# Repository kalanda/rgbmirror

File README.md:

# RGB Mirror

Controller based on Atmega8 used for modification of a Muppet's mirror to use RGB Leds.

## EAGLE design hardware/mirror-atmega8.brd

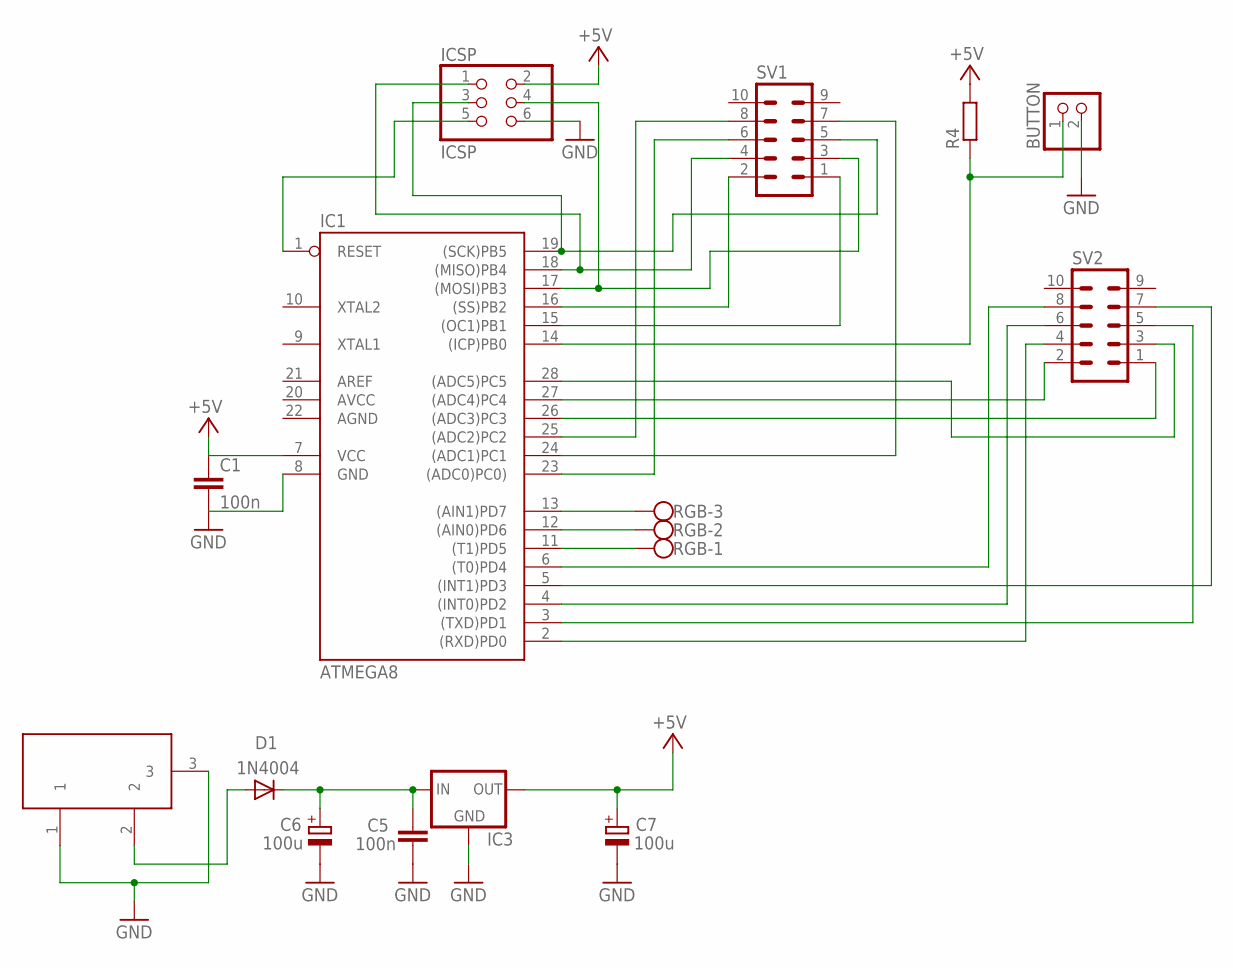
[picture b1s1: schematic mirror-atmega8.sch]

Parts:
BUTTON: PINHD-1X2; 1X02
C1, C5: 100n; C050-025X075
C6, C7: 100u; E3,5-8
D1: 1N4004; DO41-10
DC1: DC21MMX; DC-21MM
IC1: ATMEGA8; DIL28-3
IC3: 78XXL
ICSP: ICSP; 2X03
R4: R-EU_0204/7; 0204/7
RGB: W237-103
SV1, SV2: ML10

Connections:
+5V: C1.1, C7.+, IC1.7 (VCC), IC3.OUT, ICSP.2, R4.2
AGND: IC1.22 (AGND)
AREF: IC1.21 (AREF)
AVCC: IC1.20 (AVCC)
GND: BUTTON.2, C1.2, C5.1, C6.-, C7.-, DC1.1, DC1.3, IC1.8 (GND), IC3.GND, ICSP.6
unnamed: IC1.18 ((MISO)PB4), ICSP.1, SV1.4
unnamed: IC1.26 ((ADC3)PC3), SV2.1
unnamed: IC1.25 ((ADC2)PC2), SV1.8
unnamed: IC1.17 ((MOSI)PB3), ICSP.4, SV1.3
unnamed: IC1.27 ((ADC4)PC4), SV2.2
unnamed: IC1.28 ((ADC5)PC5), SV2.3
unnamed: IC1.2 ((RXD)PD0), SV2.4
unnamed: D1.A, DC1.2
unnamed: IC1.3 ((TXD)PD1), SV2.5
unnamed: IC1.4 ((INT0)PD2), SV2.6
unnamed: IC1.5 ((INT1)PD3), SV2.7
unnamed: IC1.13 ((AIN1)PD7), RGB.3
unnamed: IC1.12 ((AIN0)PD6), RGB.2
unnamed: IC1.11 ((T1)PD5), RGB.1
unnamed: IC1.6 ((T0)PD4), SV2.8
unnamed: IC1.16 ((SS)PB2), SV1.2
unnamed: BUTTON.1, IC1.14 ((ICP)PB0), R4.1
unnamed: IC1.15 ((OC1)PB1), SV1.1
unnamed: IC1.23 ((ADC0)PC0)), SV1.6
unnamed: IC1.24 ((ADC1)PC1), SV1.7
RESET: IC1.1 (RESET), ICSP.5
SCK: IC1.19 ((SCK)PB5), ICSP.3, SV1.5
VIN: C5.2, C6.+, D1.C, IC3.IN

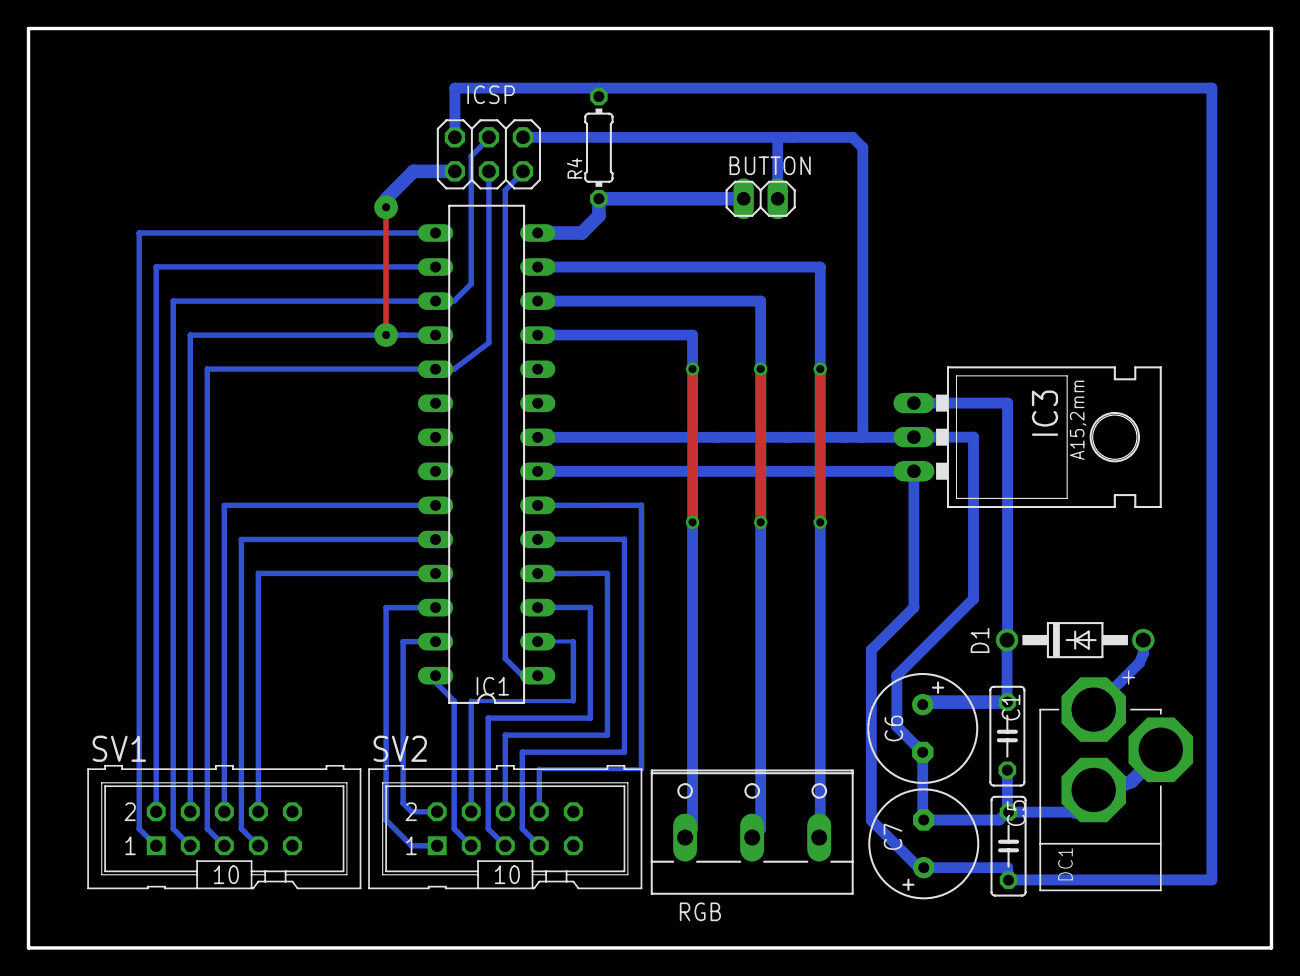
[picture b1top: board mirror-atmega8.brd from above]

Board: 2 copper layers, 92.7 x 68.6 mm, 14 parts (0 on the bottom side), 25 nets.
